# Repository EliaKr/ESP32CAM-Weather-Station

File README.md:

# ESP32CAM-Weather-Station

## Electronics

This project uses a custom weather-station PCB that combines **power management**, **protection**, and an **I2C sensor/expansion bus**.

### Power features
- Supports **battery input** with input protection.
- Supports **solar input** with surge/transient protection.
- Includes **battery charging** (status indicators and a battery temperature/thermistor input).
- Provides regulated rails for the rest of the system (including a **3.3V rail** for sensors/logic).
- Breakouts/headers for accessing power rails (battery and regulated output) for debugging or external loads.

### Measurement & sensing features
- On-board sensing for **battery voltage** and **solar/charging voltage**.
- On-board environmental sensing (temperature/humidity/pressure/gas resistance).
- On-board gas sensing (VOC/NOx measurements).
- On-board ambient light sensing (lux).
- ESP32-CAM on-board sky camera.

### I2C bus + expansion features
- I2C bus includes **pullups** and **ESD/transient protection**.
- Multiple **external I2C expansion headers** (3.3V / GND / SDA / SCL) for additional sensors.

### Extras
- A PCB that makes the board compatible with the Raspberry Pi Pico (Original or W or 2 or 2W) is also included in the design files.

### Media (photos and design files)

> Photos below are from **testing / bring-up** and may show temporary wiring or rework.

**PCB front (testing photo)**  

**PCB back (testing photo)**  

**KiCad PCB layout (screenshot)**  

**Schematic (export image)**  

---

## Mechanical design (placeholder)

- TODO: enclosure details, mounting, weatherproofing, cable glands, venting strategy, sensor placement.
- TODO: 3D print files / CAD links, tolerances, and assembly steps.
- TODO: photos/diagrams.

---

## Software: Pico Weather Station (Client) + Local Ingest Server (HTTP + HMAC)

This project consists of:

- **Client (Raspberry Pi Pico 2 W)**: reads sensors over I2C and periodically posts measurements to a server.
- **Server (Python)**: accepts measurements over **HTTP** and protects the endpoint with:
  - Bearer token allow-list (multiple devices supported)
  - HMAC-SHA256 request signature (fast reject of unauthenticated spam)
  - Rate limiting (per IP and per token)
  - Max body size and max concurrency
  - CSV logging to two files (same schema)

> Security note: This design does **not** encrypt the data in transit (it is HTTP). It **does** prevent unauthorized clients from successfully sending data (and helps prevent trivial overload). If you need confidentiality, use HTTPS.

### Repository layout (recommended)

#### PlatformIO (client)
- `src/measurement_post_requests.cpp` (or `src/main.cpp`) — client code
- `include/client_config.h` — user-created (not committed)
- `include/wificredentials.h` — user-created (not committed)

#### Server (Python)
- `server/server_config.py`
- `server/server_http_hmac.py`

---

### 1) Server setup (Python)

#### 1.1 Requirements
- Python 3.9+ recommended (stdlib only)

No pip packages required.

#### 1.2 Files
Create a directory (example):
```
server/
  server_http_hmac.py
  server_config.py
```

#### 1.3 Configure `server_config.py`
Key options:
- Bind / endpoint: `HOST`, `PORT`, `INGEST_PATH`
- Auth: `AUTH_TOKENS`, `ALLOW_BEARER_HEADER`
- Protections: `REQUIRE_HMAC`, `REQUIRE_TIMESTAMP`, `RATE_LIMIT_*`, `MAX_BODY_BYTES`, `MAX_CONCURRENT_REQUESTS`
- CSV: `CSV_PATH_1`, `CSV_PATH_2`, `CSV_HEADER`

> If you are not setting time on the Pico (no NTP), set `REQUIRE_TIMESTAMP = False`.

#### 1.4 Run the server
From the `server/` directory:
```bash
python3 server_http_hmac.py
```

#### 1.5 Test health endpoint
```bash
curl http://<server-ip>:<port>/health
```

---

### 2) Client setup (PlatformIO / Pico 2 W)

#### 2.1 Create user config headers (required)
Create these two files under the PlatformIO include directory:
- `include/client_config.h`
- `include/wificredentials.h`

These should not be committed (they contain secrets).

##### `include/wificredentials.h`
```cpp
#pragma once

#define WIFI_SSID "YOUR_WIFI_SSID"
#define WIFI_PASS "YOUR_WIFI_PASSWORD"

#define USE_STATIC_IP 1

#if USE_STATIC_IP
  #define WIFI_LOCAL_IP   IPAddress(192,168,2,55)
  #define WIFI_DNS_IP     IPAddress(1,1,1,1)
  #define WIFI_GATEWAY_IP IPAddress(192,168,2,1)
  #define WIFI_SUBNET_IP  IPAddress(255,255,255,0)
#endif
```

##### `include/client_config.h`
```cpp
#pragma once

#define DEVICE_ID "pico2w-01"
#define SERVER_URL "http://192.168.2.8:8080/ingest"

// Token secret: must exist in server_config.AUTH_TOKENS
#define AUTH_TOKEN "CHANGE_ME_TO_A_LONG_RANDOM_SECRET"

#define POST_INTERVAL_MS 1000
#define HTTP_TIMEOUT_MS 5000
```

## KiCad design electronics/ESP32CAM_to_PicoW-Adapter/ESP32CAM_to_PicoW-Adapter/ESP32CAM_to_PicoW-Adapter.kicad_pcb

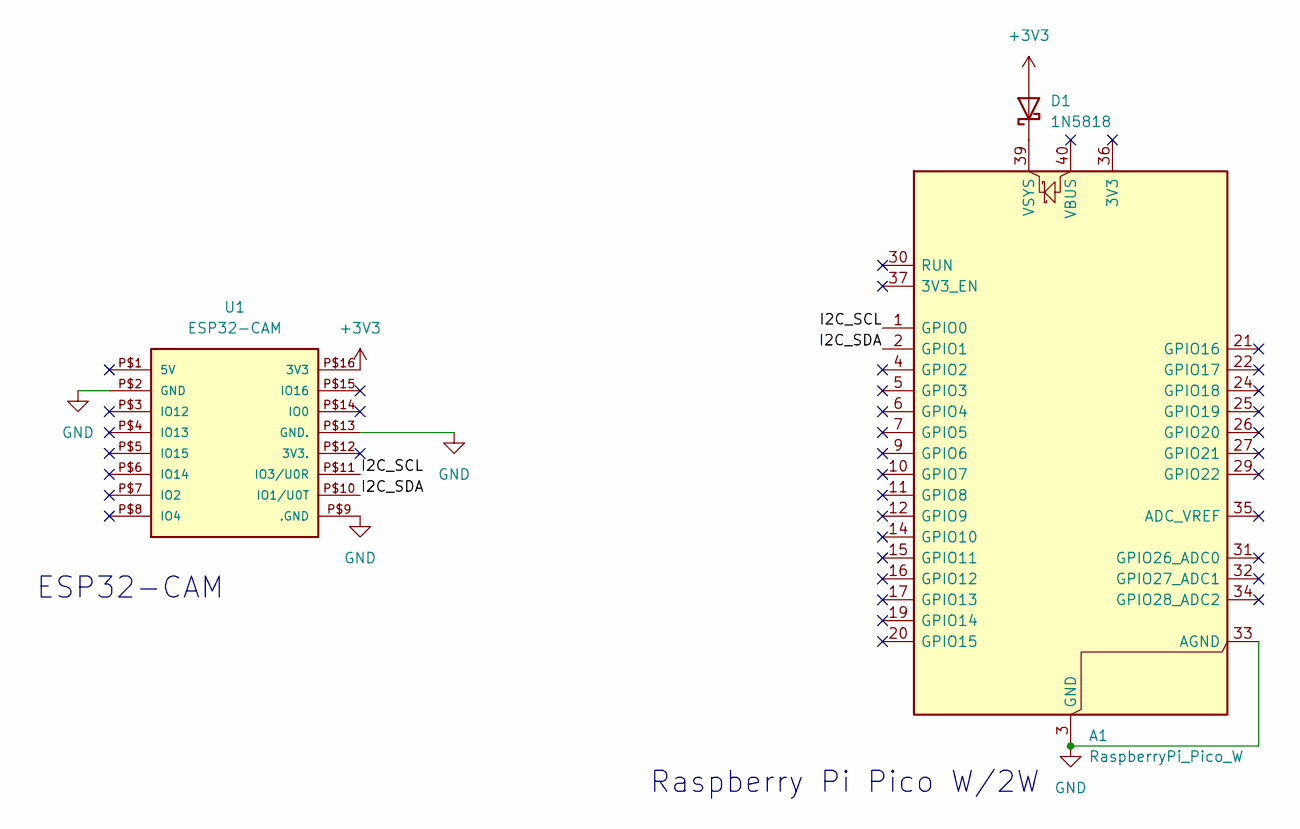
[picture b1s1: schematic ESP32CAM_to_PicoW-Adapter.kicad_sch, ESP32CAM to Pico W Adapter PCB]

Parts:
A1: RaspberryPi_Pico_W; RaspberryPi_Pico_Common_THT
D1: 1N5818; D_DO-41_SOD81_P10.16mm_Horizontal
U1: ESP32-CAM

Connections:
+3V3: D1.2 (A), U1.P$16 (3V3)
/I2C_SCL: A1.1 (GPIO0), U1.P$11 (IO3/U0R)
/I2C_SDA: A1.2 (GPIO1), U1.P$10 (IO1/U0T)
GND: A1.3 (GND), A1.8 (GND), A1.13 (GND), A1.18 (GND), A1.23 (GND), A1.28 (GND), A1.33 (AGND), A1.38 (GND), U1.P$2 (GND), U1.P$9 (.GND), U1.P$13 (GND.)
unnamed: A1.39 (VSYS), D1.1 (K)

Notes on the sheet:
ESP32-CAM
Raspberry Pi Pico W/2W

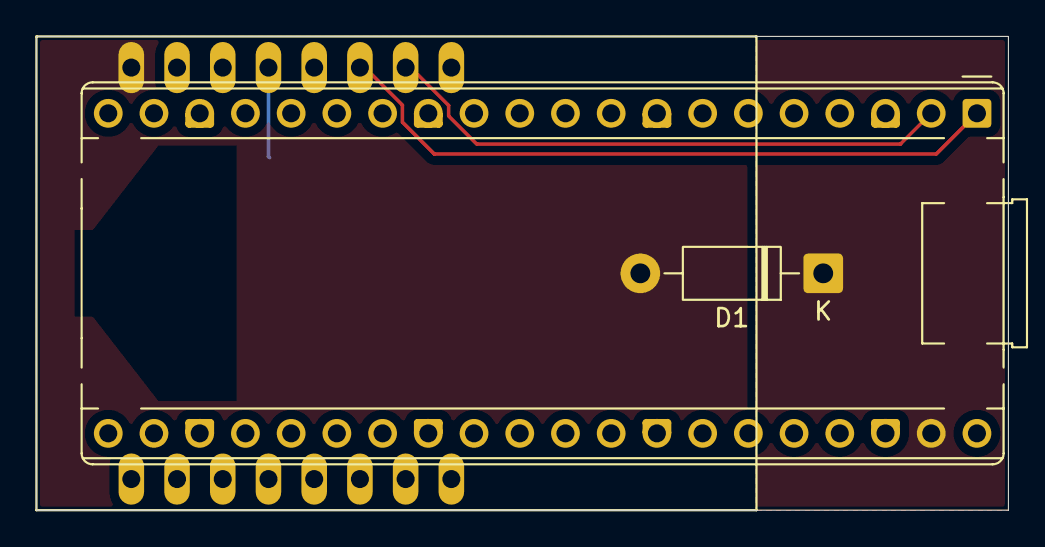
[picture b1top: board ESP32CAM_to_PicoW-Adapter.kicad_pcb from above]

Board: 2 copper layers, 54.0 x 26.3 mm, 3 parts (0 on the bottom side), 5 nets.

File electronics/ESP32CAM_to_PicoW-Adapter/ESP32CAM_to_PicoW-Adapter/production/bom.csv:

Designator,Footprint,Quantity,Value,LCSC Part #
A1,RaspberryPi_Pico_Common_THT,1,RaspberryPi_Pico_W,
D1,D_DO-41_SOD81_P10.16mm_Horizontal,1,1N5818,
U1,ESP32-CAM,1,ESP32-CAM,

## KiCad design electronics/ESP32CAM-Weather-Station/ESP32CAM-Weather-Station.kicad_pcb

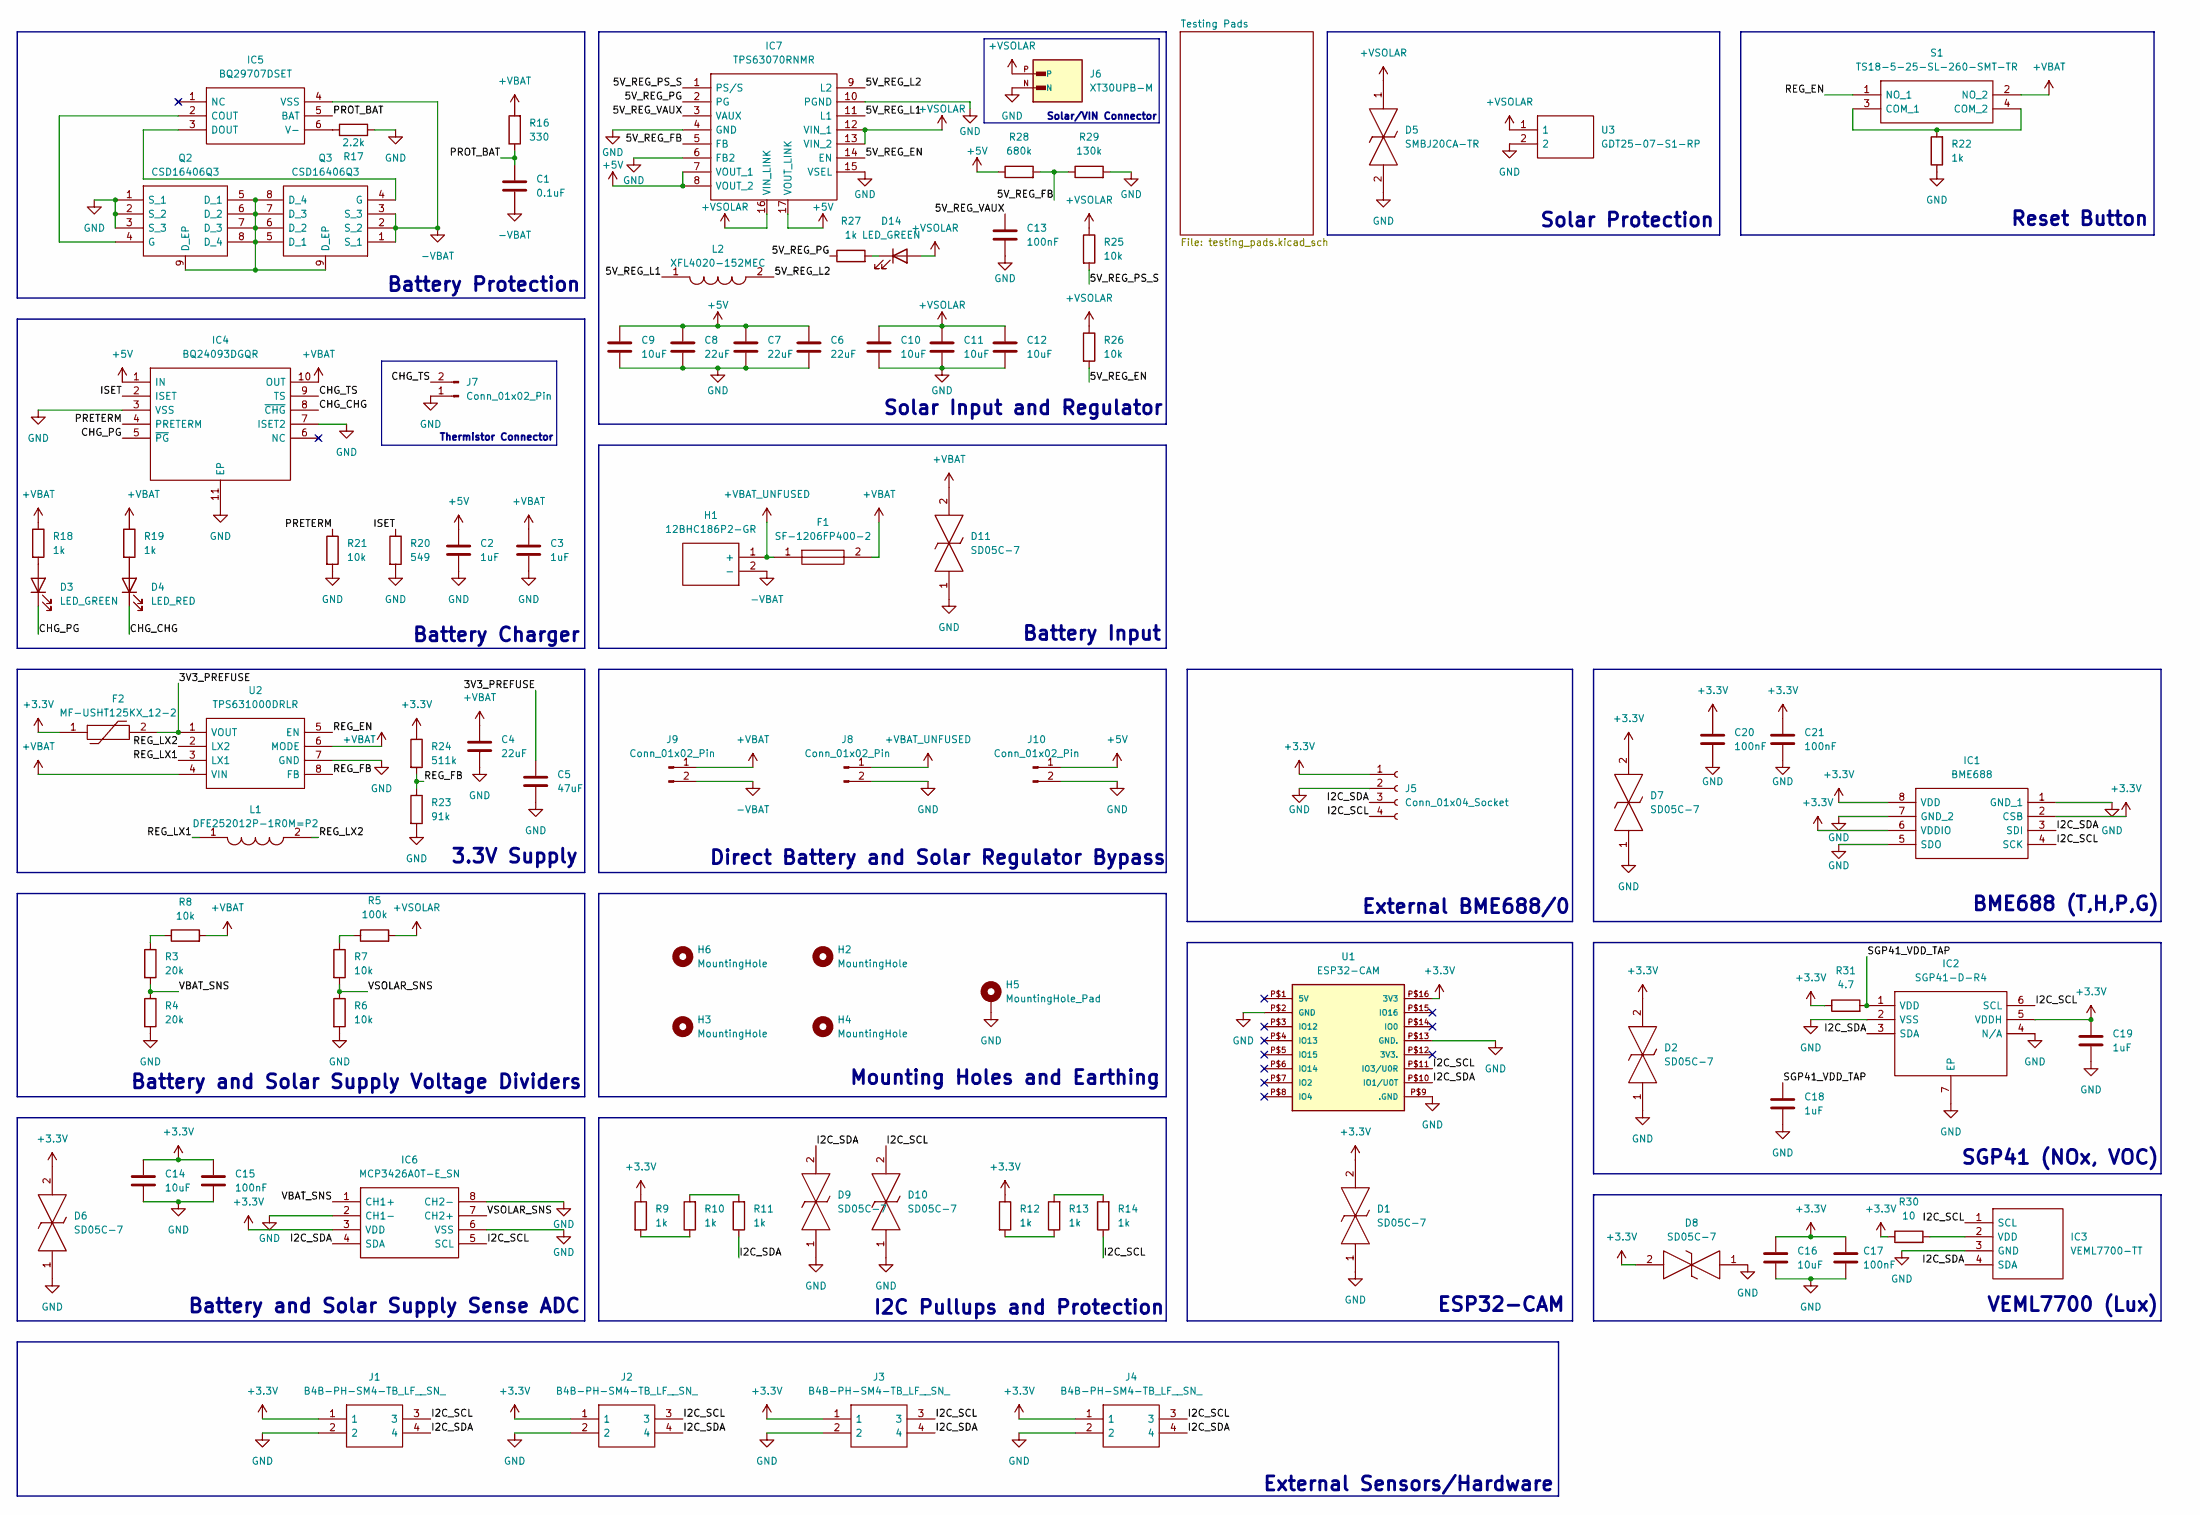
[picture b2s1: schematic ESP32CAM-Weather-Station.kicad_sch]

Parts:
C1: 0.1uF; C_0805_2012Metric_Pad1.18x1.45mm_HandSolder
C2, C3, C18, C19: 1uF; C_0805_2012Metric_Pad1.18x1.45mm_HandSolder
C4: 22uF; C_0603_1608Metric_Pad1.08x0.95mm_HandSolder
C5: 47uF; C_0805_2012Metric_Pad1.18x1.45mm_HandSolder
C6, C7, C8: 22uF; C_0805_2012Metric_Pad1.18x1.45mm_HandSolder
C9, C10: 10uF; C_0603_1608Metric_Pad1.08x0.95mm_HandSolder
C11, C12, C14, C16: 10uF; C_0805_2012Metric_Pad1.18x1.45mm_HandSolder
C13, C15, C17, C20, C21: 100nF; C_0603_1608Metric_Pad1.08x0.95mm_HandSolder
D1, D2, D6, D7, D8, D9, D10, D11: SD05C-7; SOD2513X120N; Mouser Part Number 621-SD05C-7
D3, D14: LED_GREEN; LED_0805_2012Metric_Pad1.15x1.40mm_HandSolder
D4: LED_RED; LED_0805_2012Metric_Pad1.15x1.40mm_HandSolder
D5: SMBJ20CA-TR; DIONM5436X265N; Mouser Part Number 511-SMBJ20CA
F1: SF-1206FP400-2; FUSC3116X70N; Mouser Part Number 652-SF-1206FP400-2
F2: MF-USHT125KX_12-2; MFUSHT125KX122; Mouser Part Number 652-MF-USHT125KX/12
H1: 12BHC186P2-GR; 12BHC186P2GR; Mouser Part Number 12BHC186P2-GR
H2, H3, H4, H6: MountingHole; MountingHole_3.2mm_M3_Pad_Via
H5: MountingHole_Pad; MountingHole_3.2mm_M3_DIN965_Pad
IC1: BME688; Mouser Part Number 262-BME688
IC2: SGP41-D-R4; SON80P244X244X95-7N; Mouser Part Number 403-SGP41-D-R4
IC3: VEML7700-TT; VEML7700; Mouser Part Number 78-VEML7700-TT
IC4: BQ24093DGQR; SOP50P490X110-11N; Mouser Part Number 595-BQ24093DGQR
IC5: BQ29707DSET; TPS610985DSET; Mouser Part Number 595-BQ29707DSET
IC6: MCP3426A0T-E_SN; SOIC127P600X175-8N; Mouser Part Number 579-MCP3426A0TE/SN
IC7: TPS63070RNMR; TPS630701RNMR; Mouser Part Number 595-TPS63070RNMR
J1, J2, J3, J4: B4B-PH-SM4-TB_LF__SN_; B4B-PH-SM4_1; Mouser Part Number N/A
J5: Conn_01x04_Socket; PinHeader_1x04_P2.54mm_Vertical
J6: XT30UPB-M; AMASS_XT30UPB-M
J7, J8, J9, J10: Conn_01x02_Pin; PinHeader_1x02_P2.54mm_Vertical
L1: DFE252012P-1R0M=P2; DFE2HCAH1R0MJ0L; Mouser Part Number 81-DFE252012P-1R0MP2
L2: XFL4020-152MEC; XFL4020152MEC; Mouser Part Number 994-XFL4020-152MEC
Q2, Q3: CSD16406Q3; DQG_VSON-CLIP; Mouser Part Number 595-CSD16406Q3
R3, R4: 20k; R_0805_2012Metric_Pad1.20x1.40mm_HandSolder
R5: 100k; R_0805_2012Metric_Pad1.20x1.40mm_HandSolder
R6, R7, R8, R21, R25, R26: 10k; R_0805_2012Metric_Pad1.20x1.40mm_HandSolder
R9, R10, R11, R12, R13, R14, R18, R19, R22, R27: 1k; R_0805_2012Metric_Pad1.20x1.40mm_HandSolder
R16: 330; R_0805_2012Metric_Pad1.20x1.40mm_HandSolder
R17: 2.2k; R_0805_2012Metric_Pad1.20x1.40mm_HandSolder
R20: 549; R_0805_2012Metric_Pad1.20x1.40mm_HandSolder
R23: 91k; R_0805_2012Metric_Pad1.20x1.40mm_HandSolder
R24: 511k; R_0805_2012Metric_Pad1.20x1.40mm_HandSolder
R28: 680k; R_0805_2012Metric_Pad1.20x1.40mm_HandSolder
R29: 130k; R_0805_2012Metric_Pad1.20x1.40mm_HandSolder
R30: 10; R_0805_2012Metric_Pad1.20x1.40mm_HandSolder
R31: 4.7; R_0805_2012Metric_Pad1.20x1.40mm_HandSolder
S1: TS18-5-25-SL-260-SMT-TR; TS18525SL260SMTTR; Mouser Part Number 179-TS18525SL260SMTT
U1: ESP32-CAM
U2: TPS631000DRLR; SOTFL50P160X60-8N; Mouser Part Number 595-TPS631000DRLR
U3: GDT25-07-S1-RP; GDT2507S1RP; Mouser Part Number 652-GDT25-07-S1-RP

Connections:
+3.3V: C14.1, C15.2, C16.1, C17.2, C19.1, C20.2, C21.2, D1.2, D2.2, D6.2, D7.2, D8.2, F2.1, IC1.2 (CSB), IC1.6 (VDDIO), IC1.8 (VDD), IC2.5 (VDDH), IC6.3 (VDD), J1.1, J2.1, J3.1, J4.1, J5.1, R9.1, R12.1, R24.1, R30.1, R31.1, U1.P$16 (3V3)
+5V: C2.1, C6.1, C7.1, C8.1, C9.1, IC4.1 (IN), IC7.7 (VOUT_1), IC7.8 (VOUT_2), IC7.17 (VOUT_LINK), J10.1, R28.1
+VBAT: C3.1, C4.1, D11.2, F1.2, IC4.10 (OUT), J9.1, R8.2, R16.2, R18.1, R19.1, S1.2 (NO_2), U2.4 (VIN), U2.6 (MODE)
+VBAT_UNFUSED: F1.1, H1.1 (+), J8.1
+VSOLAR: C10.1, C11.1, C12.1, D5.1, D14.2 (A), IC7.12 (VIN_1), IC7.13 (VIN_2), IC7.16 (VIN_LINK), J6.P, R5.2, R25.1, R26.1, U3.1
-VBAT: C1.2, H1.2 (-), IC5.4 (VSS), J9.2, Q3.1 (S_1), Q3.2 (S_2), Q3.3 (S_3)
/3V3_PREFUSE: C5.1, F2.2, U2.1 (VOUT)
/5V_REG_EN: IC7.14 (EN), R26.2
/5V_REG_FB: IC7.5 (FB), R28.2, R29.1
/5V_REG_L1: IC7.11 (L1), L2.1
/5V_REG_L2: IC7.9 (L2), L2.2
/5V_REG_PG: IC7.2 (PG), R27.1
/5V_REG_PS_S: IC7.1 (PS/S), R25.2
/5V_REG_VAUX: C13.2, IC7.3 (VAUX)
/CHG_CHG: D4.1 (K), IC4.8 (~CHG)
/CHG_PG: D3.1 (K), IC4.5 (~PG)
/CHG_TS: IC4.9 (TS), J7.2
/I2C_SCL: D10.2, IC1.4 (SCK), IC2.6 (SCL), IC3.1 (SCL), IC6.5 (SCL), J1.3, J2.3, J3.3, J4.3, J5.4, R14.1, U1.P$11 (IO3/U0R)
/I2C_SDA: D9.2, IC1.3 (SDI), IC2.3 (SDA), IC3.4 (SDA), IC6.4 (SDA), J1.4, J2.4, J3.4, J4.4, J5.3, R11.1, U1.P$10 (IO1/U0T)
/ISET: IC4.2 (ISET), R20.1
/PRETERM: IC4.4 (PRETERM), R21.1
/PROT_BAT: C1.1, IC5.5 (BAT), R16.1
/REG_EN: S1.1 (NO_1), U2.5 (EN)
/REG_FB: R23.1, R24.2, U2.8 (FB)
/REG_LX1: L1.1, U2.3 (LX1)
/REG_LX2: L1.2, U2.2 (LX2)
/SGP41_VDD_TAP: C18.1, IC2.1 (VDD), R31.2
/VBAT_SNS: IC6.1 (CH1+), R3.2, R4.1
/VSOLAR_SNS: IC6.7 (CH2+), R6.1, R7.2
GND: C2.2, C3.2, C4.2, C5.2, C6.2, C7.2, C8.2, C9.2, C10.2, C11.2, C12.2, C13.1, C14.2, C15.1, C16.2, C17.1, C18.2, C19.2, C20.1, C21.1, D1.1, D2.1, D5.2, D6.1, D7.1, D8.1, D9.1, D10.1, D11.1, H5.1, IC1.1 (GND_1), IC1.5 (SDO), IC1.7 (GND_2), IC2.2 (VSS), IC2.4 (N/A), IC2.7 (EP), IC3.3 (GND), IC4.3 (VSS), IC4.7 (ISET2), IC4.11 (EP), IC6.2 (CH1-), IC6.6 (VSS), IC6.8 (CH2-), IC7.4 (GND), IC7.6 (FB2), IC7.10 (PGND), IC7.15 (VSEL), J1.2, J2.2, J3.2, J4.2, J5.2, J6.N, J7.1, J8.2, J10.2, Q2.1 (S_1), Q2.2 (S_2), Q2.3 (S_3), R4.2, R6.2, R17.1, R20.2, R21.2, R22.1, R23.2, R29.2, U1.P$2 (GND), U1.P$9 (.GND), U1.P$13 (GND.), U2.7 (GND), U3.2
unnamed: D3.2 (A), R18.2
unnamed: D4.2 (A), R19.2
unnamed: D14.1 (K), R27.2
unnamed: IC3.2 (VDD), R30.2
unnamed: IC5.2 (COUT), Q2.4 (G)
unnamed: IC5.3 (DOUT), Q3.4 (G)
unnamed: IC5.6 (V-), R17.2
unnamed: Q2.5 (D_1), Q2.6 (D_2), Q2.7 (D_3), Q2.8 (D_4), Q2.9 (D_EP), Q3.5 (D_1), Q3.6 (D_2), Q3.7 (D_3), Q3.8 (D_4), Q3.9 (D_EP)
unnamed: R3.1, R8.1
unnamed: R5.1, R7.1
unnamed: R9.2, R10.1
unnamed: R10.2, R11.2
unnamed: R12.2, R13.1
unnamed: R13.2, R14.2
unnamed: R22.2, S1.3 (COM_1), S1.4 (COM_2)

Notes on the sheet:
SGP41 (NOx, VOC)
Mounting Holes and Earthing
Battery and Solar Supply Voltage Dividers
3.3V Supply
Battery and Solar Supply Sense ADC
Battery Charger
Battery Protection
Solar/VIN Connector
I2C Pullups and Protection
Battery Input
External Sensors/Hardware
ESP32-CAM
Direct Battery and Solar Regulator Bypass
Reset Button
Solar Input and Regulator
External BME688/0
Solar Protection
VEML7700 (Lux)
BME688 (T,H,P,G)
Thermistor Connector

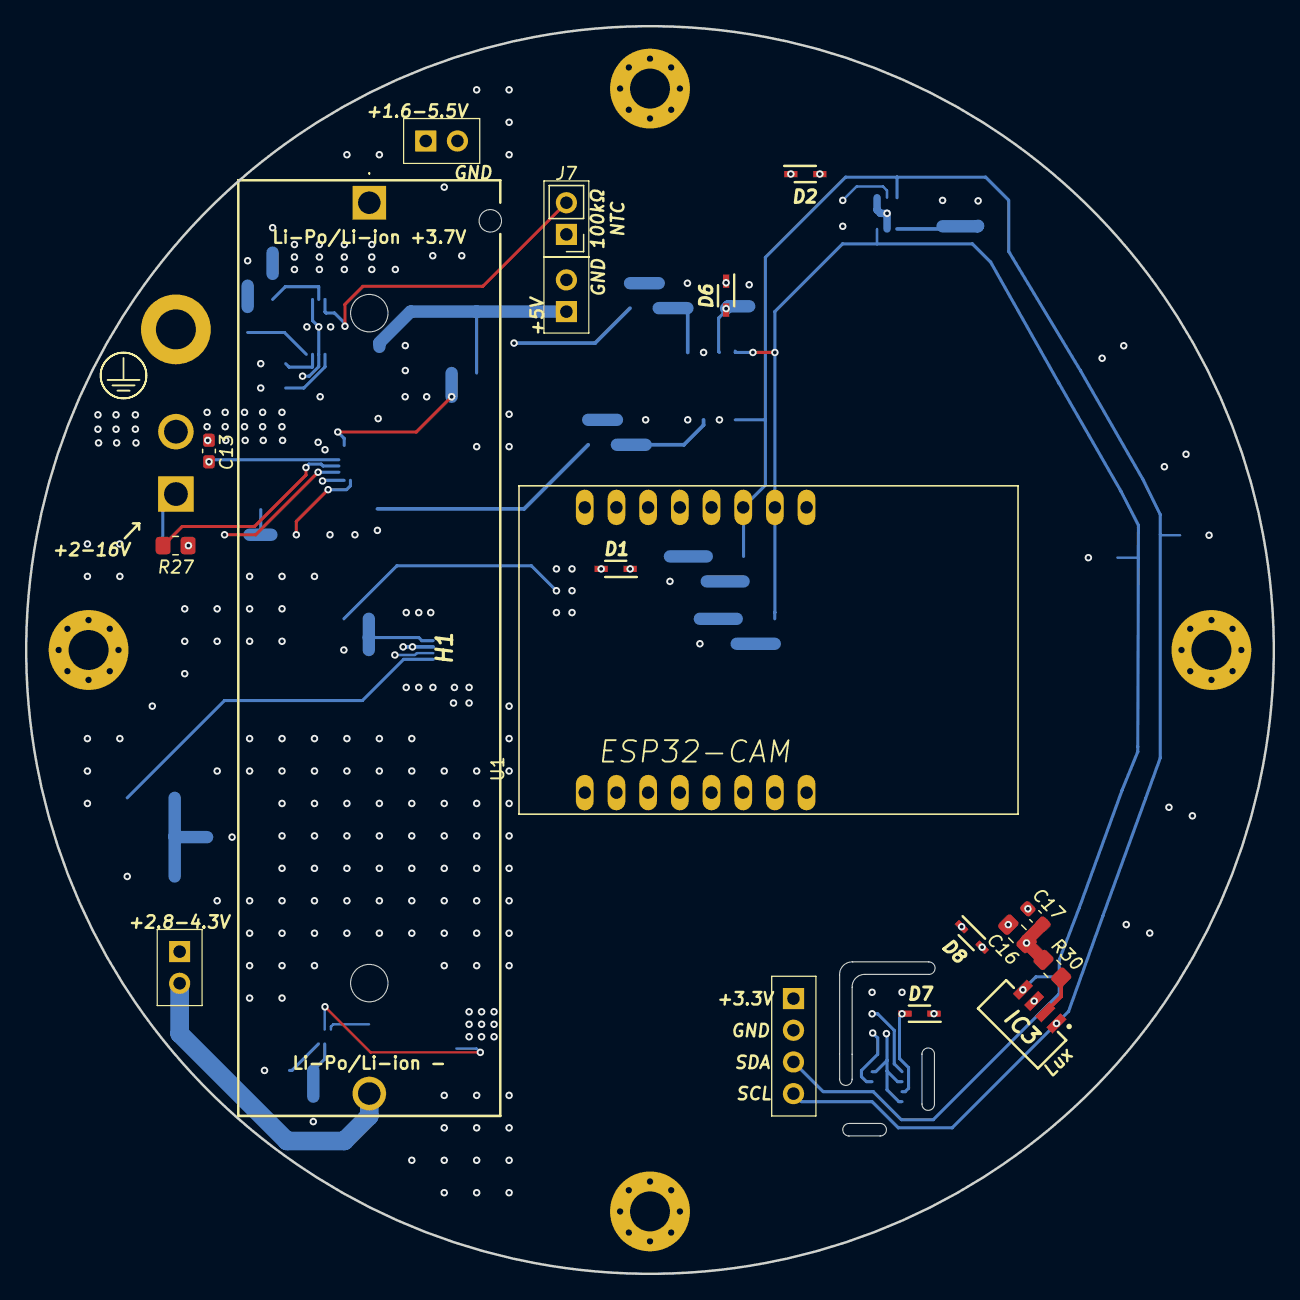
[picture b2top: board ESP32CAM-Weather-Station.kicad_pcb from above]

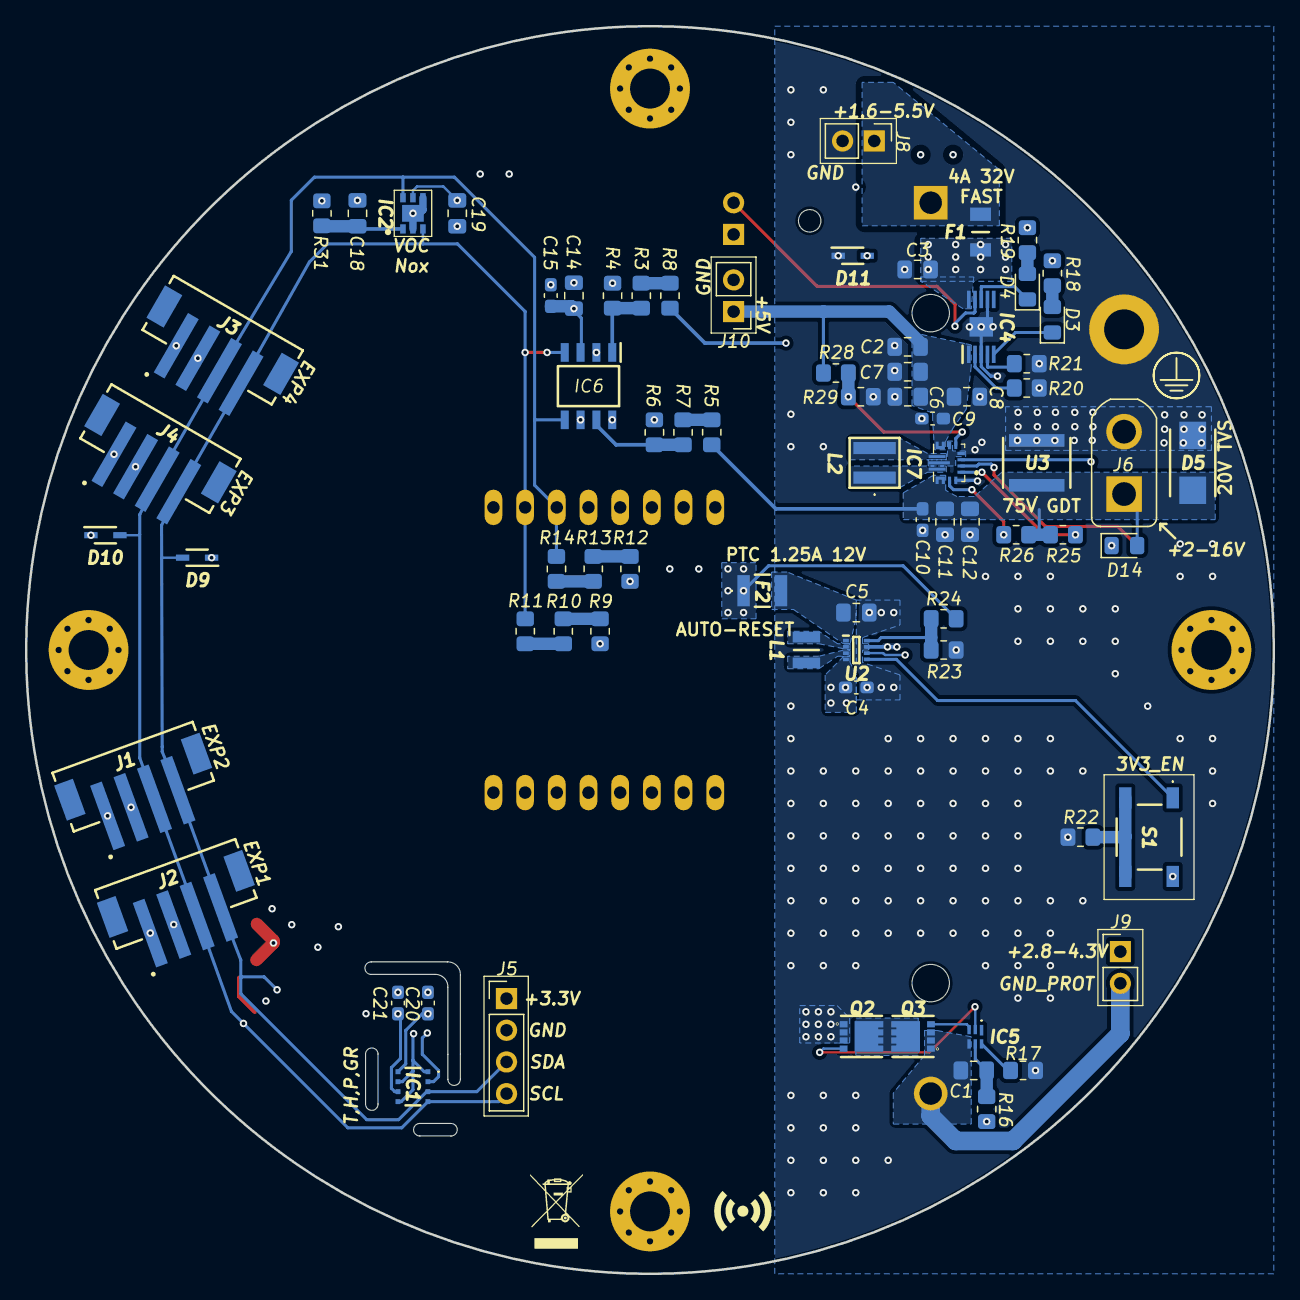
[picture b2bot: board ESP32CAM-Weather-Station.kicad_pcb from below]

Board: 4 copper layers, 100.0 x 100.0 mm, 94 parts (75 on the bottom side), 45 nets.

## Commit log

2026-01-11 Initial KiCad project creation commit.
2026-01-11 [WIP] Included libraries and setup board.
2026-01-11 [WIP] Placed basic parts.
2026-01-12 [WIP] Added battery access header, I2C pullups and ADC voltage dividers.
2026-01-12 [WIP] Added ESP32-CAM, I2C Pullup, JST Connections.
2026-01-12 [WIP] Connected GPIO pins to LEDs, Buzzer.
2026-01-12 [WIP] Wired battery input and protection.
2026-01-12 [WIP] Wired battery charger for 1A charge current and 500mA preterm current.
2026-01-12 [WIP] Wired 3v3 regulator.
2026-01-13 [WIP] Added transient protection and mounting holes.
2026-01-13 [WIP] Routed solar input regulator.
2026-01-13 [WIP] Routed ADC and buzzer.
2026-01-13 [WIP] Routed light sensor.
2026-01-13 [WIP] Routed SGP41.
2026-01-13 [WIP] Routed BME688.
2026-01-13 [Ready for review] Final schematic housekeeping. Removed unusable I/O due to pin constraints (camera and SD)
2026-01-13 [Self-review] Slight cosmetic fix.
2026-01-15 [WIP] Added board shape.
2026-01-15 [WIP] Marked placement restrictions
2026-01-15 [WIP] Placed Basic Connectors.
2026-01-15 [WIP] Placed main battery protection components.
2026-01-15 [WIP] Placed basic 3v3 regulator parts.
2026-01-15 [WIP] Placed basic 5V regulator parts and moved 3V3 regulator so that output connects to the 3V3 plane.
2026-01-15 [WIP] Placed all power components.
2026-01-15 [WIP] Completed most of the placement and routing.
2026-01-16 [WIP] Power stage routed. Created board cutouts for BME688.
2026-01-16 [Ready for review, Passes DRC] Routing completed.
2026-01-16 [Self-review] Added via stiching on power supply side ground.
2026-01-16 [Misc.] Added FreeSans font.
2026-01-16 [WIP] Silkscreen, designator design and placement completed.
2026-01-17 [WIP] Added basic functional silkscreen markings.
2026-01-17 [Ready for review] Added final graphics.
2026-01-17 [Self review] Removed floating copper from bottom layer.
2026-01-17 [Self review] Reverted previous edit to prevent prepreg fill, grounded copper.
2026-01-17 [Final] Removed lck files.
2026-01-19 Added mechanical files.
2026-02-09 [WIP] Added platformio project and code structure.
2026-02-09 [WIP] Add gitkeeps
2026-02-09 [WIP] Added some testing code
2026-03-14 [Final] Added ESP32CAM to PicoW adapter.
2026-03-14 [Fix] Silkscreen fix on adapter board.
2026-03-14 Added testing code for the Raspberry Pi Pico. Board verified, all components operational.
2026-03-14 Added python plotting script and voic,nox index.
2026-03-14 Added code for testing over WiFi.
2026-03-15 Removed blocking serial delay.
2026-03-15 Add wificredentials.h for Wi-Fi configuration
    This file contains Wi-Fi credentials and static IP configuration for the Pico2W Weather Station.
2026-03-15 Added placeholder for measurement logging by post requests to server.
2026-03-15 Added server code and pico POST request code.
2026-03-15 Added measurement interval define.
2026-03-15 Add README for ESP32CAM Weather Station project
    Added detailed project documentation for the ESP32CAM Weather Station, including electronics, software setup, and client/server configuration.
2026-03-15 Added cleaner photos.
2026-03-15 Added lower power mode by disconnecting wifi between measurements.
2026-03-15 Add configuration file for SFTP plotting
